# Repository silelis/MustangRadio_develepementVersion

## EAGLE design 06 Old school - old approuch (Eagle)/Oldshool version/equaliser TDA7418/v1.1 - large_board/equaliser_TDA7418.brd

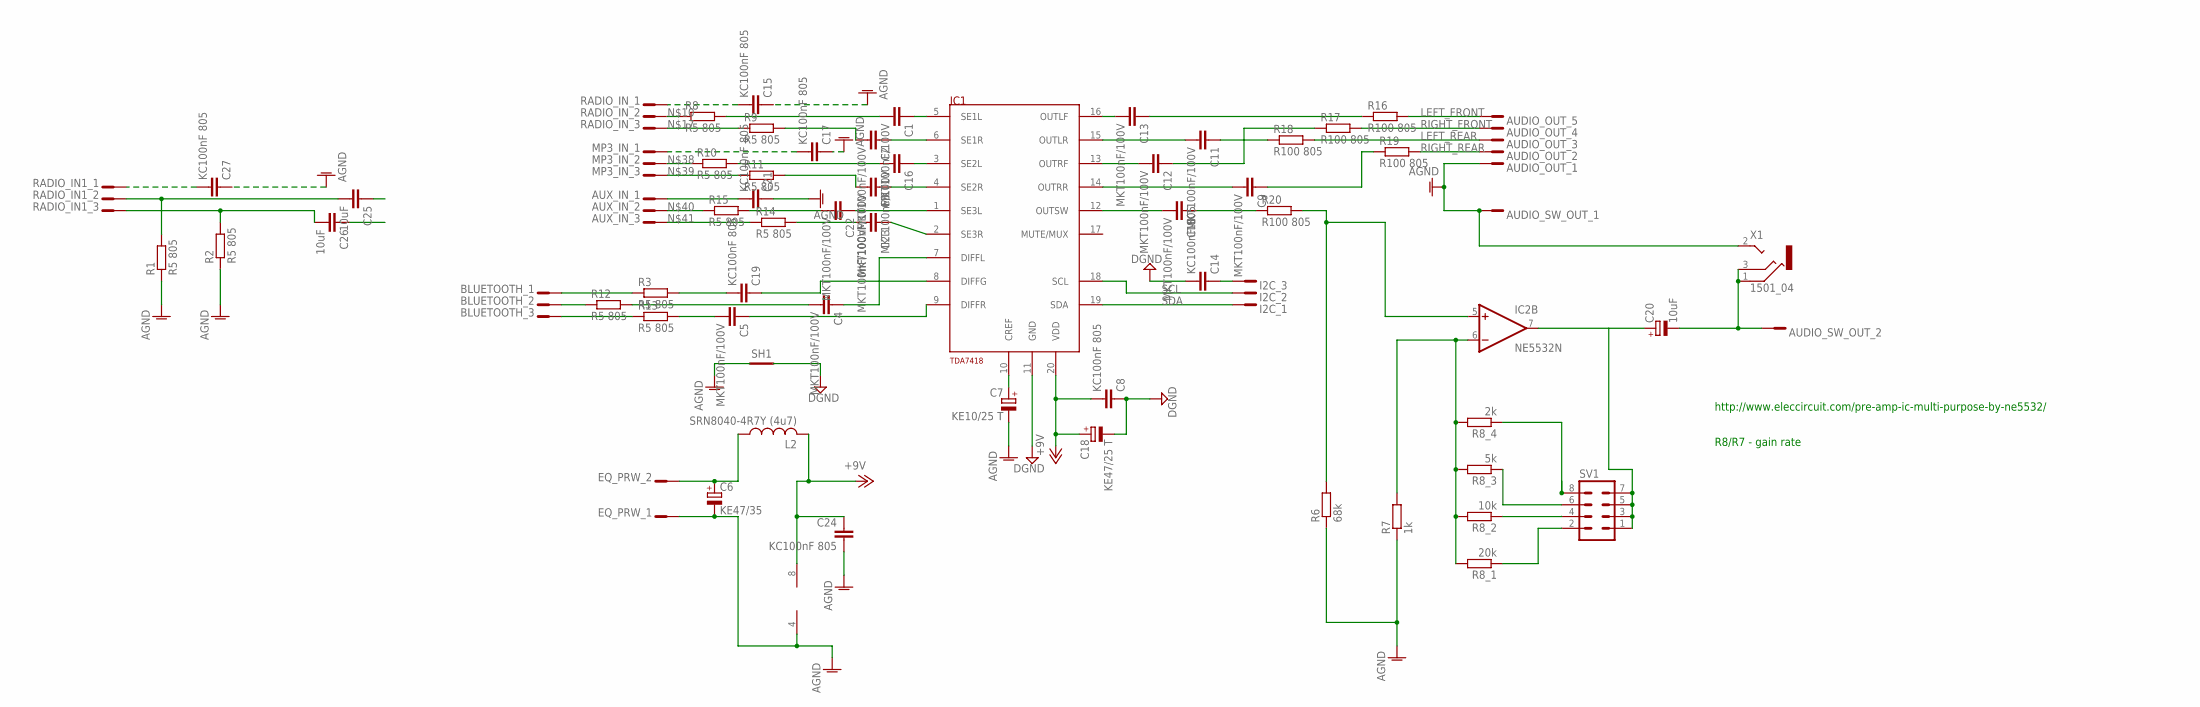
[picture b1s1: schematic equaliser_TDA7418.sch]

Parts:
AUDIO_OUT: JST_5_PIN_B5B-PH-KS; B5B-PH-KS
AUDIO_SW_OUT: JST_2_PIN_B2B-PH-KS; B2B-PH-KS
AUX_IN: JST_3_PIN_B3B-PH-KS; B3B-PH-KS
BLUETOOTH: JST_3_PIN_B3B-PH-KS; B3B-PH-KS
C1, C2, C3, C4, C5, C9, C10, C11, C12, C13, C16, C22, C23: MKT100nF/100V; C050-035X075
C6: KE47/35; TT2D6
C7: KE10/25 T; E1,8-4
C8, C14, C15, C17, C19, C21, C24, C27: KC100nF 805; C0805
C18: KE47/25 T; B45181B
C20: 10uF; TT2D6
C25, C26: 10uF; C050-035X075
EQ_PRW: JST_2_PIN_B2B-XH-A; B2B-XH-A
I2C: JST_3_PIN_B3B-PH-KS; B3B-PH-KS
IC1: TDA7418; SO20
IC2: NE5532N; DIL08
L2: SRN8040-4R7Y (4u7); 0204/5
MP3_IN: JST_3_PIN_B3B-PH-KS; B3B-PH-KS
R1, R2, R3, R8, R9, R10, R11, R12, R13, R14, R15: R5 805; R0805
R6: 68k; R0805
R7: 1k; R0805
R8_1: 20k; R0805
R8_2: 10k; R0805
R8_3: 5k; R0805
R8_4: 2k; R0805
R16, R17, R18, R19, R20: R100 805; R0805
RADIO_IN, RADIO_IN1: JST_3_PIN_B3B-PH-KS; B3B-PH-KS
SH1: SHORT-HT5; SHORT_TOP-50
SV1: MA04-2
X1: 1501_04; 1501_05

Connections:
+9V0: C8.2, C18.+, C24.1, IC1.20 (VDD), IC2.8 (V+), L2.2
AGND: AUDIO_OUT.P$1, AUDIO_SW_OUT.P$1, C6.-, C7.-, C15.1, C17.1, C21.1, C24.2, C27.1, EQ_PRW.P$1, IC2.4 (V-), R1.1, R2.1, R6.1, R7.1, SH1.1, X1.2
DGND: C8.1, C14.2, C18.-, IC1.11 (GND), SH1.2
L1: C1.2, R8.2
L2: C16.2, R10.2
L3: C4.2, R12.2
L4: C25.2, R1.2, RADIO_IN1.P$2
LEFT_FRONT: AUDIO_OUT.P$5, R16.2
LEFT_REAR: AUDIO_OUT.P$3, R18.2
unnamed: C6.+, EQ_PRW.P$2, L2.1
unnamed: R8_1.1, SV1.2
unnamed: C7.+, IC1.10 (CREF)
unnamed: C1.1, IC1.5 (SE1L)
unnamed: C2.1, IC1.6 (SE1R)
unnamed: C16.1, IC1.3 (SE2L)
unnamed: C3.1, IC1.4 (SE2R)
unnamed: C23.1, IC1.2 (SE3R)
unnamed: C22.1, IC1.1 (SE3L)
unnamed: R8.1, RADIO_IN.P$2
unnamed: AUDIO_SW_OUT.P$2, C20.-, X1.1, X1.3
unnamed: C13.2, IC1.16 (OUTLF)
unnamed: C11.2, IC1.15 (OUTLR)
unnamed: C11.1, R18.1
unnamed: C9.1, R19.1
unnamed: C12.2, IC1.13 (OUTRF)
unnamed: R9.1, RADIO_IN.P$3
unnamed: C9.2, IC1.14 (OUTRR)
unnamed: C10.2, IC1.12 (OUTSW)
unnamed: R8_2.1, SV1.4
unnamed: C20.+, IC2.7 (OUT), SV1.1, SV1.3, SV1.5, SV1.7
unnamed: R8_3.1, SV1.6
unnamed: C14.1, I2C.P$3
unnamed: C15.2, RADIO_IN.P$1
unnamed: C13.1, R16.1
unnamed: C17.2, MP3_IN.P$1
unnamed: BLUETOOTH.P$1, R3.1
unnamed: R8_4.1, SV1.8
unnamed: C4.1, IC1.7 (DIFFL)
unnamed: C5.1, IC1.9 (DIFFR)
unnamed: C22.2, R15.2
unnamed: AUX_IN.P$3, R14.1
unnamed: IC2.6 (-IN), R7.2, R8_1.2, R8_2.2, R8_3.2, R8_4.2
unnamed: IC2.5 (+IN), R6.2, R20.2
unnamed: C12.1, R17.1
unnamed: C10.1, R20.1
unnamed: MP3_IN.P$2, R10.1
unnamed: MP3_IN.P$3, R11.1
unnamed: BLUETOOTH.P$2, R12.1
unnamed: BLUETOOTH.P$3, R13.1
unnamed: AUX_IN.P$2, R15.1
unnamed: C23.2, R14.2
unnamed: C2.2, R9.2
unnamed: C3.2, R11.2
unnamed: C5.2, R13.2
unnamed: AUX_IN.P$1, C21.2
unnamed: C27.2, RADIO_IN1.P$1
unnamed: C19.1, IC1.8 (DIFFG)
unnamed: C26.2, R2.2, RADIO_IN1.P$3
unnamed: C19.2, R3.2
RIGHT_FRONT: AUDIO_OUT.P$4, R17.2
RIGHT_REAR: AUDIO_OUT.P$2, R19.2
SCL: I2C.P$2, IC1.18 (SCL)
SDA: I2C.P$1, IC1.19 (SDA)

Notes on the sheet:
http://www.eleccircuit.com/pre-amp-ic-multi-purpose-by-ne5532/
R8/R7 - gain rate

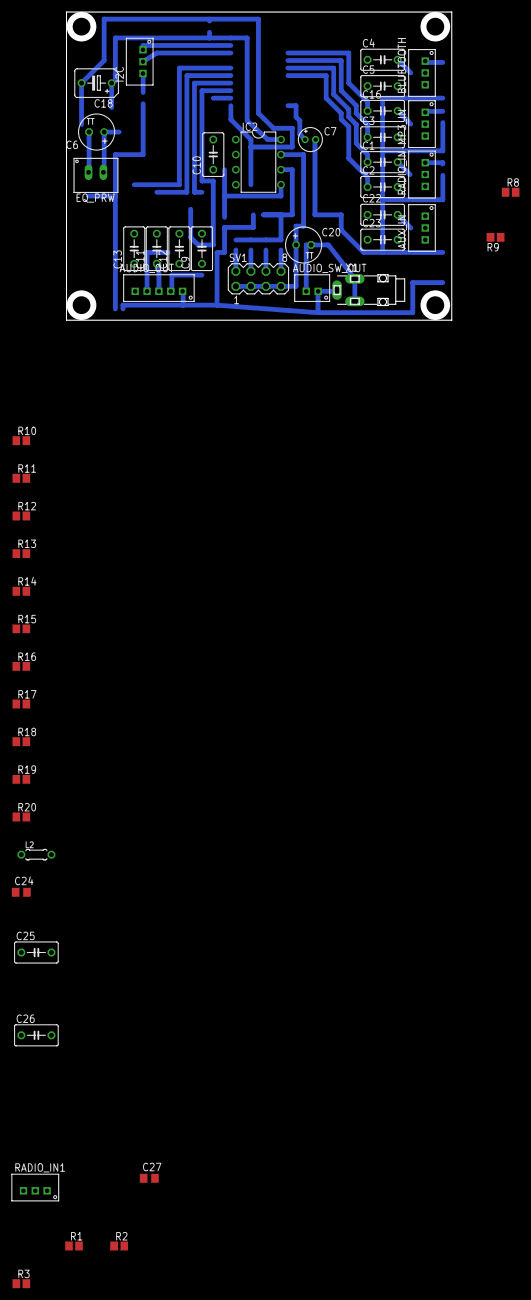
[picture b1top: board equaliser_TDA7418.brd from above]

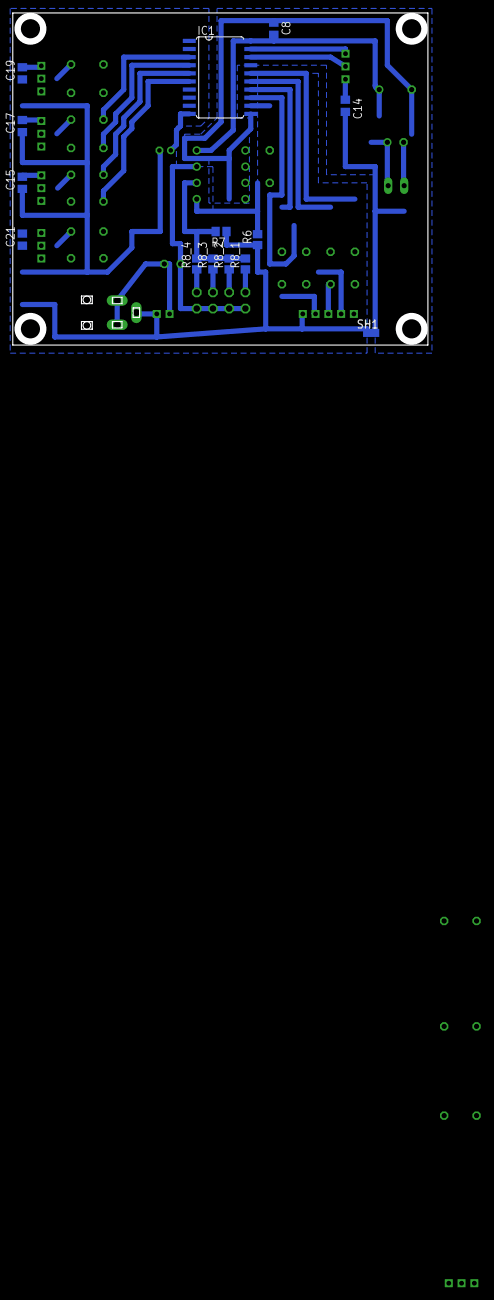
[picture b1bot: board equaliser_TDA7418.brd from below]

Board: 2 copper layers, 65.0 x 52.0 mm, 64 parts (14 on the bottom side), 63 nets.

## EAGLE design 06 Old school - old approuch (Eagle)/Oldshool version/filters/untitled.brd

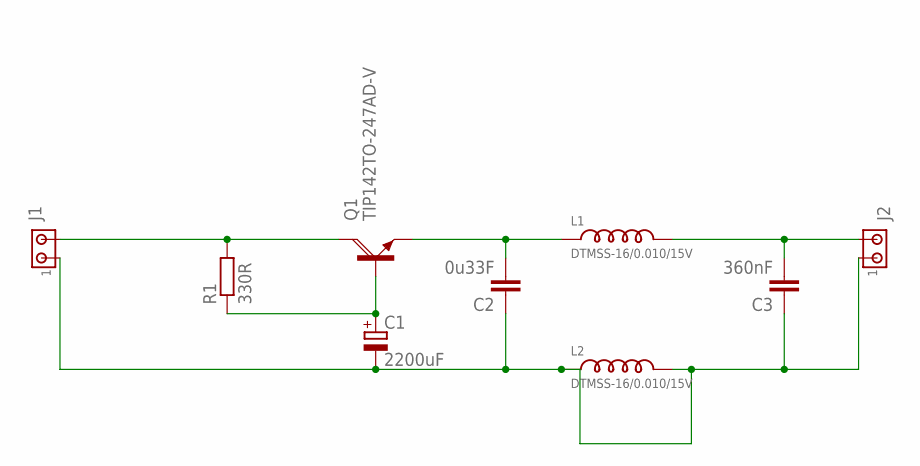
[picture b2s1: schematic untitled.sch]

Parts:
C1: 2200uF; E5-13
C2: 0u33F; C102-054X133
C3: 360nF; C102-054X133
J1, J2: MTA02-100; 10X02MTA
L1, L2: DTMSS-16/0.010/15V; DTMSS-16/0.010/15-V
Q1: TIP142TO-247AD-V; TO-247AD-V
R1: 330R; VTA52

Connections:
GND: C1.-, C2.1, C3.1, J1.1, J2.1, L2.P$1, L2.P$2
unnamed: J1.2, Q1.D (C), R1.2
unnamed: C1.+, Q1.G (B), R1.1
unnamed: C2.2, L1.P$1, Q1.S (E)
unnamed: C3.2, J2.2, L1.P$2

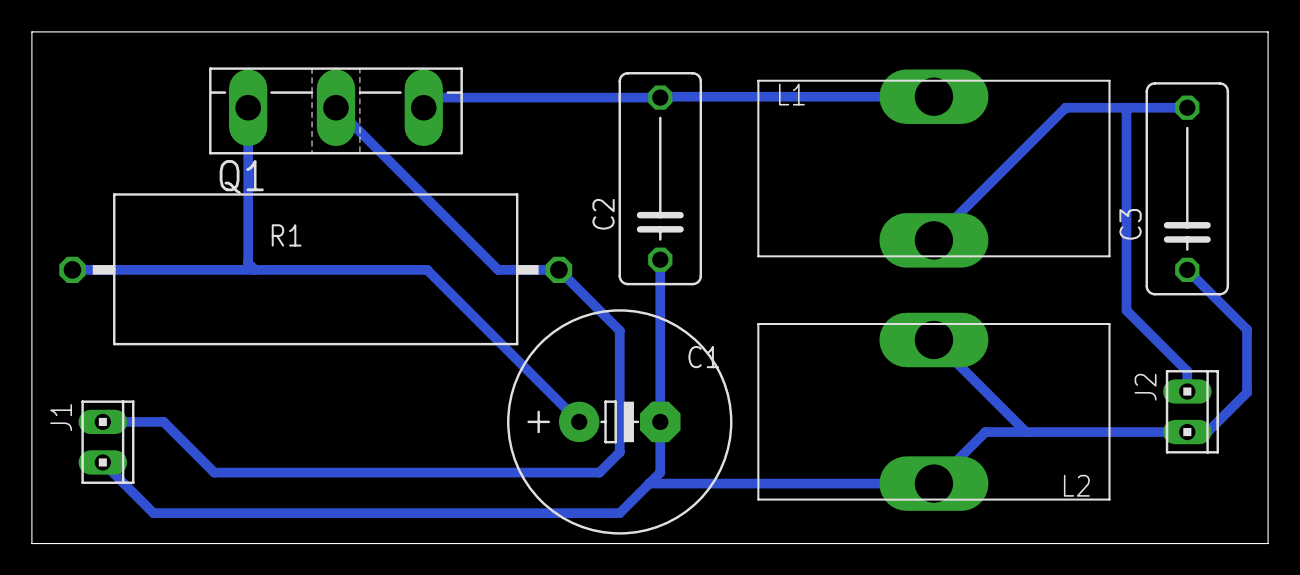
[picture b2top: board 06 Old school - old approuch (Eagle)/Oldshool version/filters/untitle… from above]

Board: 2 copper layers, 77.4 x 32.1 mm, 9 parts (0 on the bottom side), 5 nets.

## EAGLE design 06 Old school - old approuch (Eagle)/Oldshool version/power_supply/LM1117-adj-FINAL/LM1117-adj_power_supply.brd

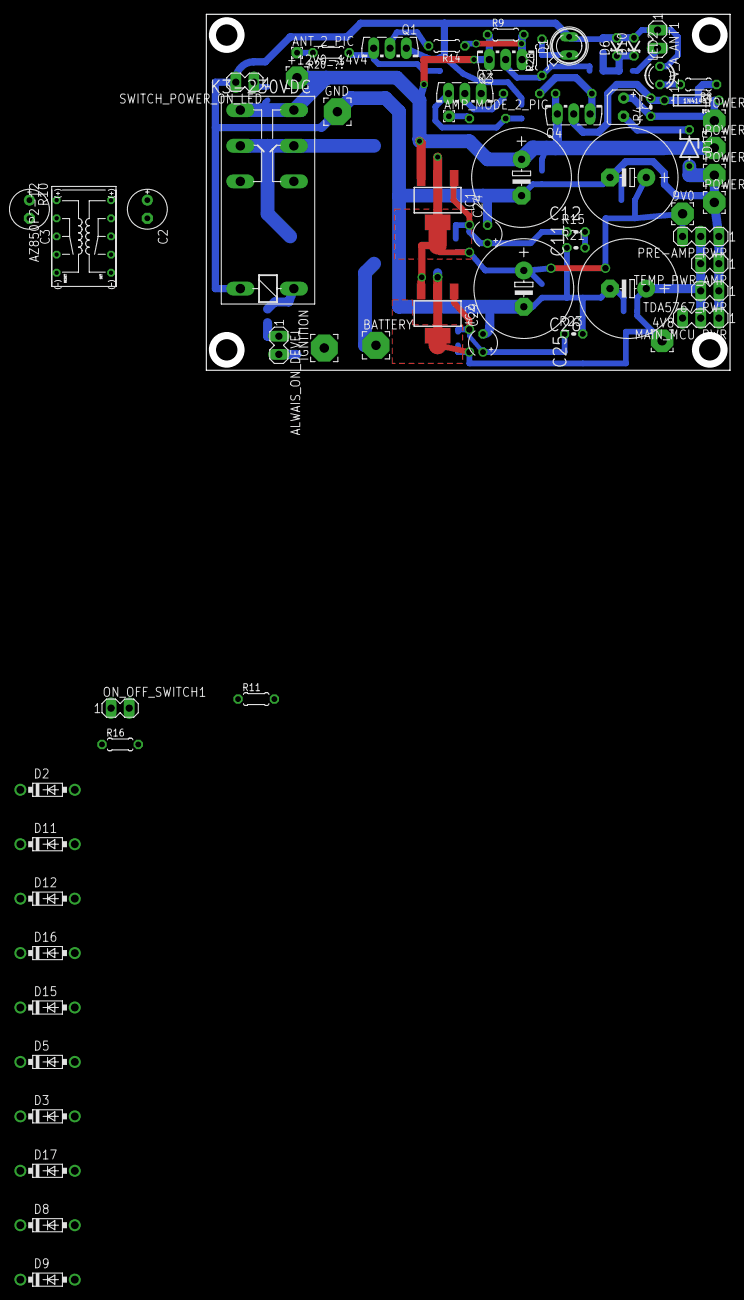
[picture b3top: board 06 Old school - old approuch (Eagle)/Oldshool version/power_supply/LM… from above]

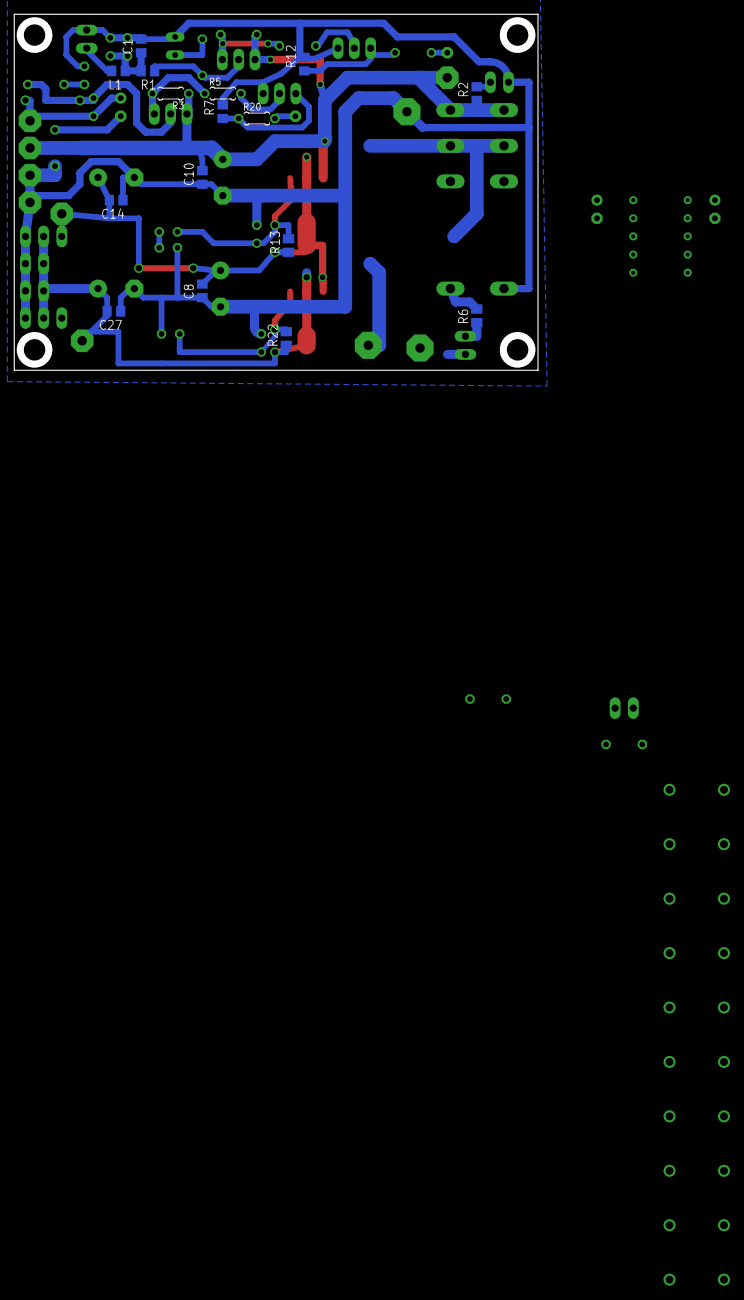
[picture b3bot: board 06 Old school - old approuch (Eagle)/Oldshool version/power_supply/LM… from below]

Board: 2 copper layers, 73.3 x 49.8 mm, 80 parts (16 on the bottom side), 36 nets.

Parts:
4V8, 9V0: 3,17/1,3
12V_A_ANT1: MA02-1
+12V0-14V4: 3,17/1,3
ALWAIS_ON_DEVEL: MA02-1
AMP_MODE_2_PIC: 1,6/0,8
ANT_2_PIC: 1,6/0,8
BATTERY: +14V4; 3,81/1,3
C1, C8, C10, C14, C27: KC100nF 805; C0805
C2, C3: 22-100uF/25V; E2,5-6E
C7: KE47/25 T; B45181A
C11, C12, C25, C26: KE2200/25; E5-13
C24, C29: KE10/50; TT2D4
D1: LED F2 G; SFH482
D2, D3, D5, D8, D9, D11, D12, D15, D16, D17: 1N4004; DO41-7.6
D6, D10: 1.3W12V; ZDIO-2.5
D13: 3.9V; ZDIO-5
D14: 1N4148; DO-1N4148
GND: GND; 3,81/1,3
IC1, IC2: LM1117MPX-ADJ; SOT223
IGNITION: +14V4; 3,81/1,3
K3-230VDC: AZ743-2CB-12DE; G2R2
L1: R600@100M; R0805
LED2: LED F3 B; LED3MM
MAIN_MCU_PWR: MA03-1
ON_OFF_SWITCH1: MA02-1
POWER_AMP_1, POWER_AMP_2, POWER_AMP_3: 3,17/1,3
POWER_AMP_MODE: 3,17/1,3
PRE-AMP_PWR: MA03-1
Q1, Q2: BD139; TO126AV
Q3, Q4: BD136; TO126AV
R1: R240 805; M0805
R2: R1K; R0805
R3, R9: R10K; 0204/5
R4: 10k; 0204V
R5: R4.7; 0204/5
R6: R??? 805 1; M0805
R7, R12: R10K 805; R0805
R8, R20, R20-??, R28: R1K; 0204/5
R10: AZ850P2-12; AZ850-2C
R11, R16: 2.2k-5k; 0204/5
R13, R22: R240 805 1; M0805
R14: R4.7K; 0204/5
R15, R21, R23: R680 1%; 0204V
SWITCH_POWER_ON_LED: MA02-1
TDA5767_PWR: MA02-1
TEMP_PWR_AMP: MA02-1

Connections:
+4V8: 4V8.1, C26.+, C27.2, D3.A, D17.C, IC2.2, IC2.TAB, MAIN_MCU_PWR.2, PRE-AMP_PWR.2, R22.1, TDA5767_PWR.2, TEMP_PWR_AMP.2
+9V0: 9V0.1, C8.2, C12.+, C14.2, C25.+, D3.C, D8.A, D9.C, IC1.2, IC1.TAB, IC2.3, PRE-AMP_PWR.3, R13.1
+14.4V: +12V0-14V4.1, C10.2, C11.+, D8.C, IC1.3, K3-230VDC.S1, K3-230VDC.S2, POWER_AMP_3.1, Q3.E, Q4.E, R2.1, R3.1, R9.1
AMP_MODE: AMP_MODE_2_PIC.1, R20.2
GND: 12V_A_ANT1.1, C1.2, C8.1, C10.1, C11.-, C12.-, C14.1, C24.-, C25.-, C26.-, C27.1, C29.-, D1.K, D5.A, D6.A, D10.A, D13.A, GND.1, K3-230VDC.2, LED2.K, MAIN_MCU_PWR.1, ON_OFF_SWITCH1.1, POWER_AMP_1.1, POWER_AMP_2.1, PRE-AMP_PWR.1, Q1.E, Q2.E, R7.2, R12.2, R21.1, R23.2, SWITCH_POWER_ON_LED.2, TDA5767_PWR.1, TEMP_PWR_AMP.1
MCLR_SUPPLY: ALWAIS_ON_DEVEL.1, R6.1, R10.P$7
MCLR_SUPPLY1: ALWAIS_ON_DEVEL.2, D15.C
unnamed: ANT_2_PIC.1, R20-??.2
unnamed: C24.+, D9.A, IC1.1, R13.2, R15.1
unnamed: R15.2, R21.2
unnamed: D2.A, D11.A, R10.P$5
unnamed: BATTERY.1, K3-230VDC.P1, K3-230VDC.P2, R10.P$3
unnamed: Q3.C, R1.1, R28.1
unnamed: D5.C, K3-230VDC.1, R6.2
unnamed: R2.2, SWITCH_POWER_ON_LED.1
unnamed: D14.C, Q4.C, R4.2, R8.1
unnamed: D15.A, IGNITION.1
unnamed: C2.+, D2.C, R10.P$1, R11.1
unnamed: C3.+, D16.C, R10.P$10, R16.1
unnamed: Q1.B, R12.1, R20-??.1
unnamed: Q1.C, R14.2
unnamed: C2.-, C3.-, D11.C, D12.C, ON_OFF_SWITCH1.2
unnamed: C7.-, D13.C
unnamed: C7.+, D14.A, POWER_AMP_MODE.1, R4.1
unnamed: D12.A, D16.A, R10.P$6
unnamed: Q3.B, R9.2, R14.1
unnamed: C1.1, D6.C, D10.C, L1.1, R1.2
unnamed: C29.+, D17.A, IC2.1, R22.2, R23.1
unnamed: R10.P$4, R11.2
unnamed: R10.P$2, R16.2
unnamed: 12V_A_ANT1.2, L1.2
unnamed: D1.A, R28.2
unnamed: Q2.B, R7.1, R20.1
unnamed: Q2.C, R5.2
unnamed: Q4.B, R3.2, R5.1
unnamed: LED2.A, R8.2

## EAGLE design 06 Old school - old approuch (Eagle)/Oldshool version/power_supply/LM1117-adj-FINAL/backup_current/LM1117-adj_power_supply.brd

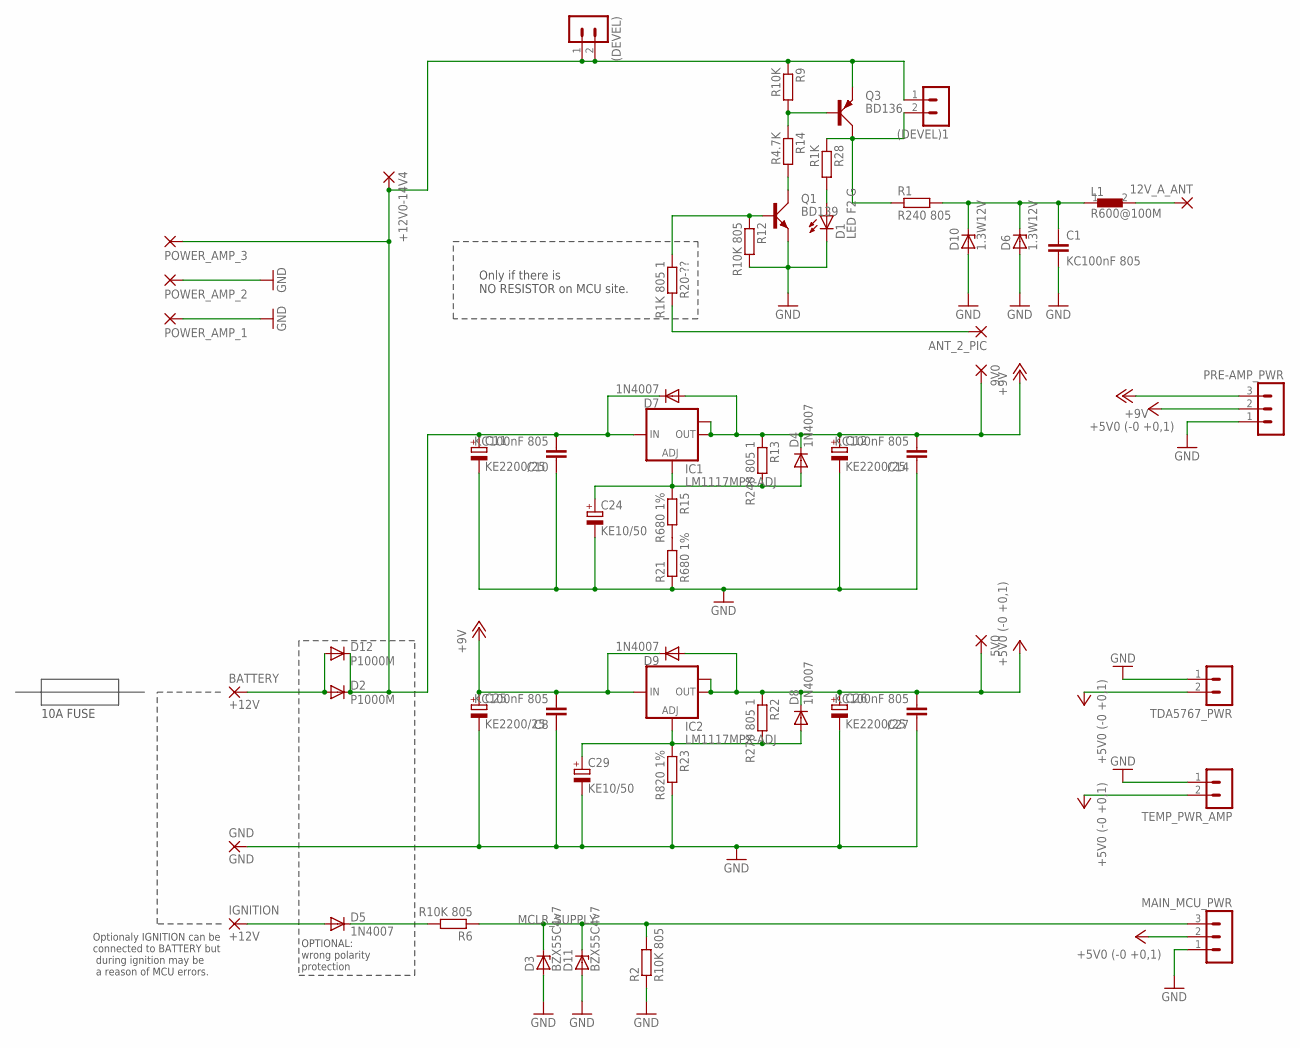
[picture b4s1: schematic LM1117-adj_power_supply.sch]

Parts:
5V0, 9V0, 12V_A_ANT: 3,17/1,3
(DEVEL), (DEVEL)1: MA02-1
+12V0-14V4: 3,17/1,3
ANT_2_PIC: 1,6/0,8
BATTERY: +12V; 3,81/1,3
C1, C8, C10, C14, C27: KC100nF 805; C0805
C11, C12, C25, C26: KE2200/25; E5-13
C24, C29: KE10/50; TT2D4
D1: LED F2 G; SFH482
D2, D12: P1000M; P6-15
D3, D11: BZX55C4v7; ZDIO-2.5
D4, D8: 1N4007; D-2.5
D5, D7, D9: 1N4007; D-5
D6, D10: 1.3W12V; ZDIO-2.5
GND: GND; 3,81/1,3
IC1, IC2: LM1117MPX-ADJ; SOT223
IGNITION: +12V; 3,81/1,3
L1: R600@100M; R0805
MAIN_MCU_PWR: MA03-1
POWER_AMP_1, POWER_AMP_2, POWER_AMP_3: 3,17/1,3
PRE-AMP_PWR: MA03-1
Q1: BD139; TO126AV
Q3: BD136; TO126AV
R1: R240 805; M0805
R2, R6, R12: R10K 805; R0805
R9: R10K; 0204/5
R13: R240 805 1; M0805
R14: R4.7K; 0204/5
R15, R21: R680 1%; 0204V
R20-??: R1K 805 1; 0204V
R22: R270 805 1; M0805
R23: R820 1%; 0204V
R28: R1K; 0204/5
TDA5767_PWR: MA02-1
TEMP_PWR_AMP: MA02-1

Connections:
+5V: 5V0.1, C26.+, C27.2, D8.C, D9.A, IC2.2 (OUT), IC2.TAB (OUT1), MAIN_MCU_PWR.2, PRE-AMP_PWR.2, R22.1, TDA5767_PWR.2, TEMP_PWR_AMP.2
+12V: 9V0.1, C8.2, C12.+, C14.2, C25.+, D4.C, D7.A, D9.C, IC1.2 (OUT), IC1.TAB (OUT1), IC2.3 (IN), PRE-AMP_PWR.3, R13.1
+14.4V: (DEVEL).1, (DEVEL).2, (DEVEL)1.1, +12V0-14V4.1, C10.2, C11.+, D2.C, D7.C, D12.C, IC1.3 (IN), POWER_AMP_3.1, Q3.E, R9.1
GND: C1.2, C8.1, C10.1, C11.-, C12.-, C14.1, C24.-, C25.-, C26.-, C27.1, C29.-, D1.K (C), D3.A, D6.A, D10.A, D11.A, GND.1, MAIN_MCU_PWR.1, POWER_AMP_1.1, POWER_AMP_2.1, PRE-AMP_PWR.1, Q1.E, R2.1, R12.2, R21.1, R23.2, TDA5767_PWR.1, TEMP_PWR_AMP.1
MCLR_SUPPLY: D3.C, D11.C, MAIN_MCU_PWR.3, R2.2, R6.1
unnamed: ANT_2_PIC.1, R20-??.2
unnamed: C24.+, D4.A, IC1.1 (ADJ), R13.2, R15.1
unnamed: R15.2, R21.2
unnamed: BATTERY.1, D2.A, D12.A
unnamed: (DEVEL)1.2, Q3.C, R1.1, R28.1
unnamed: D5.A, IGNITION.1
unnamed: D5.C, R6.2
unnamed: Q1.B, R12.1, R20-??.1
unnamed: Q1.C, R14.2
unnamed: Q3.B, R9.2, R14.1
unnamed: C1.1, D6.C, D10.C, L1.1, R1.2
unnamed: C29.+, D8.A, IC2.1 (ADJ), R22.2, R23.1
unnamed: 12V_A_ANT.1, L1.2
unnamed: D1.A, R28.2

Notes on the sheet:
10A FUSE
Optionaly IGNITION can be connected to BATTERY but during ignition may be a reason of MCU errors.
OPTIONAL: wrong polarity protection
Only if there is NO RESISTOR on MCU site.

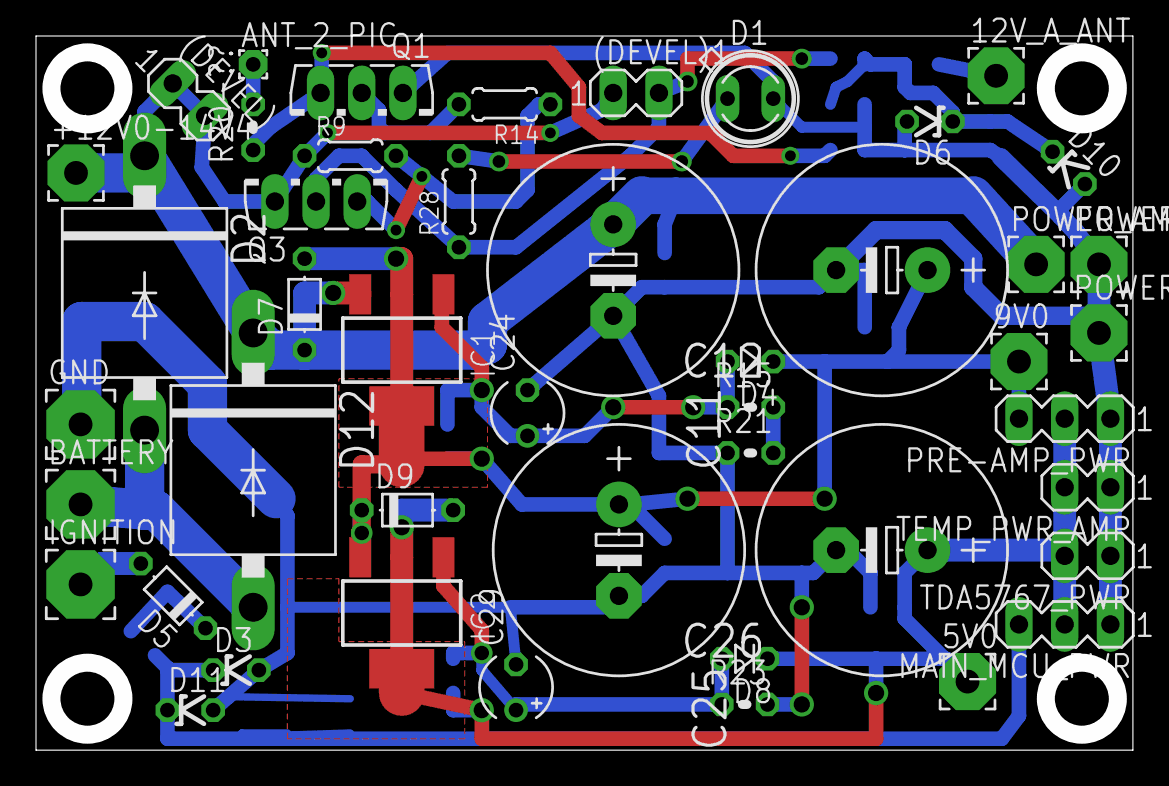
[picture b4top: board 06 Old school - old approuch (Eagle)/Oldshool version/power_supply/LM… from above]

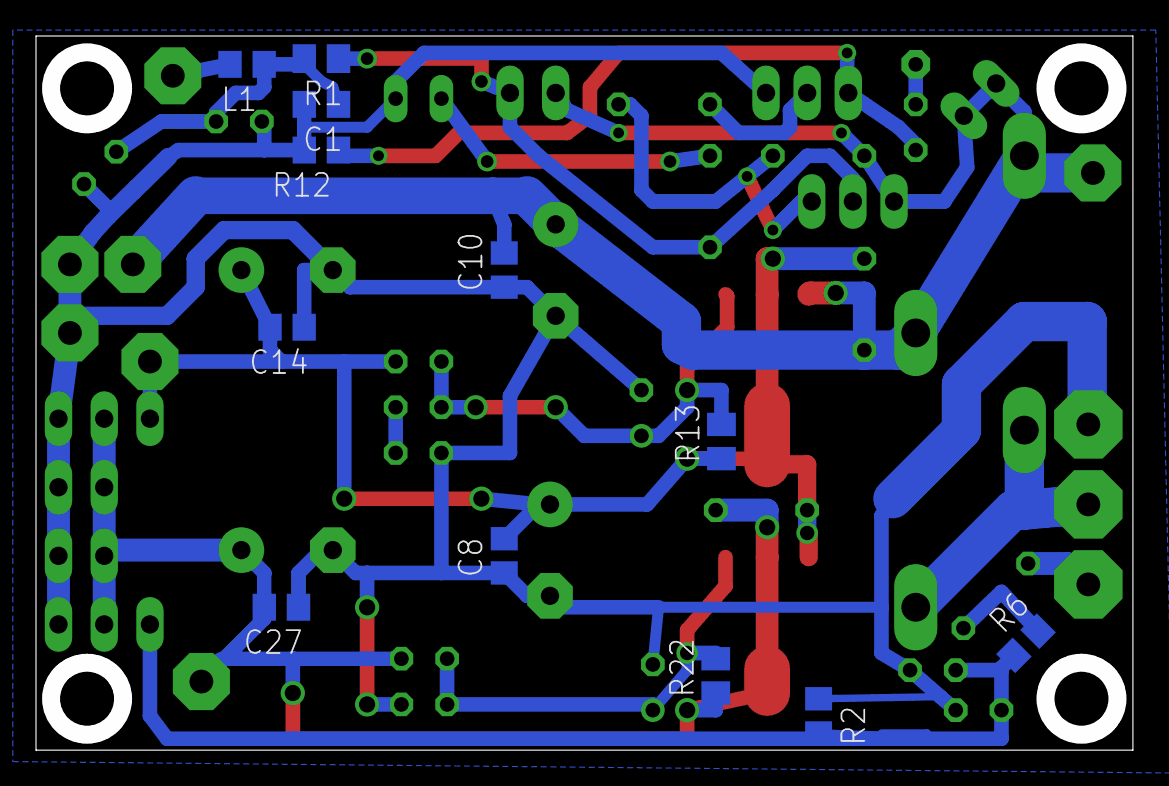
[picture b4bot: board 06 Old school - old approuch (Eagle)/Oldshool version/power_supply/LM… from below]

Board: 2 copper layers, 60.9 x 39.7 mm, 58 parts (12 on the bottom side), 19 nets.

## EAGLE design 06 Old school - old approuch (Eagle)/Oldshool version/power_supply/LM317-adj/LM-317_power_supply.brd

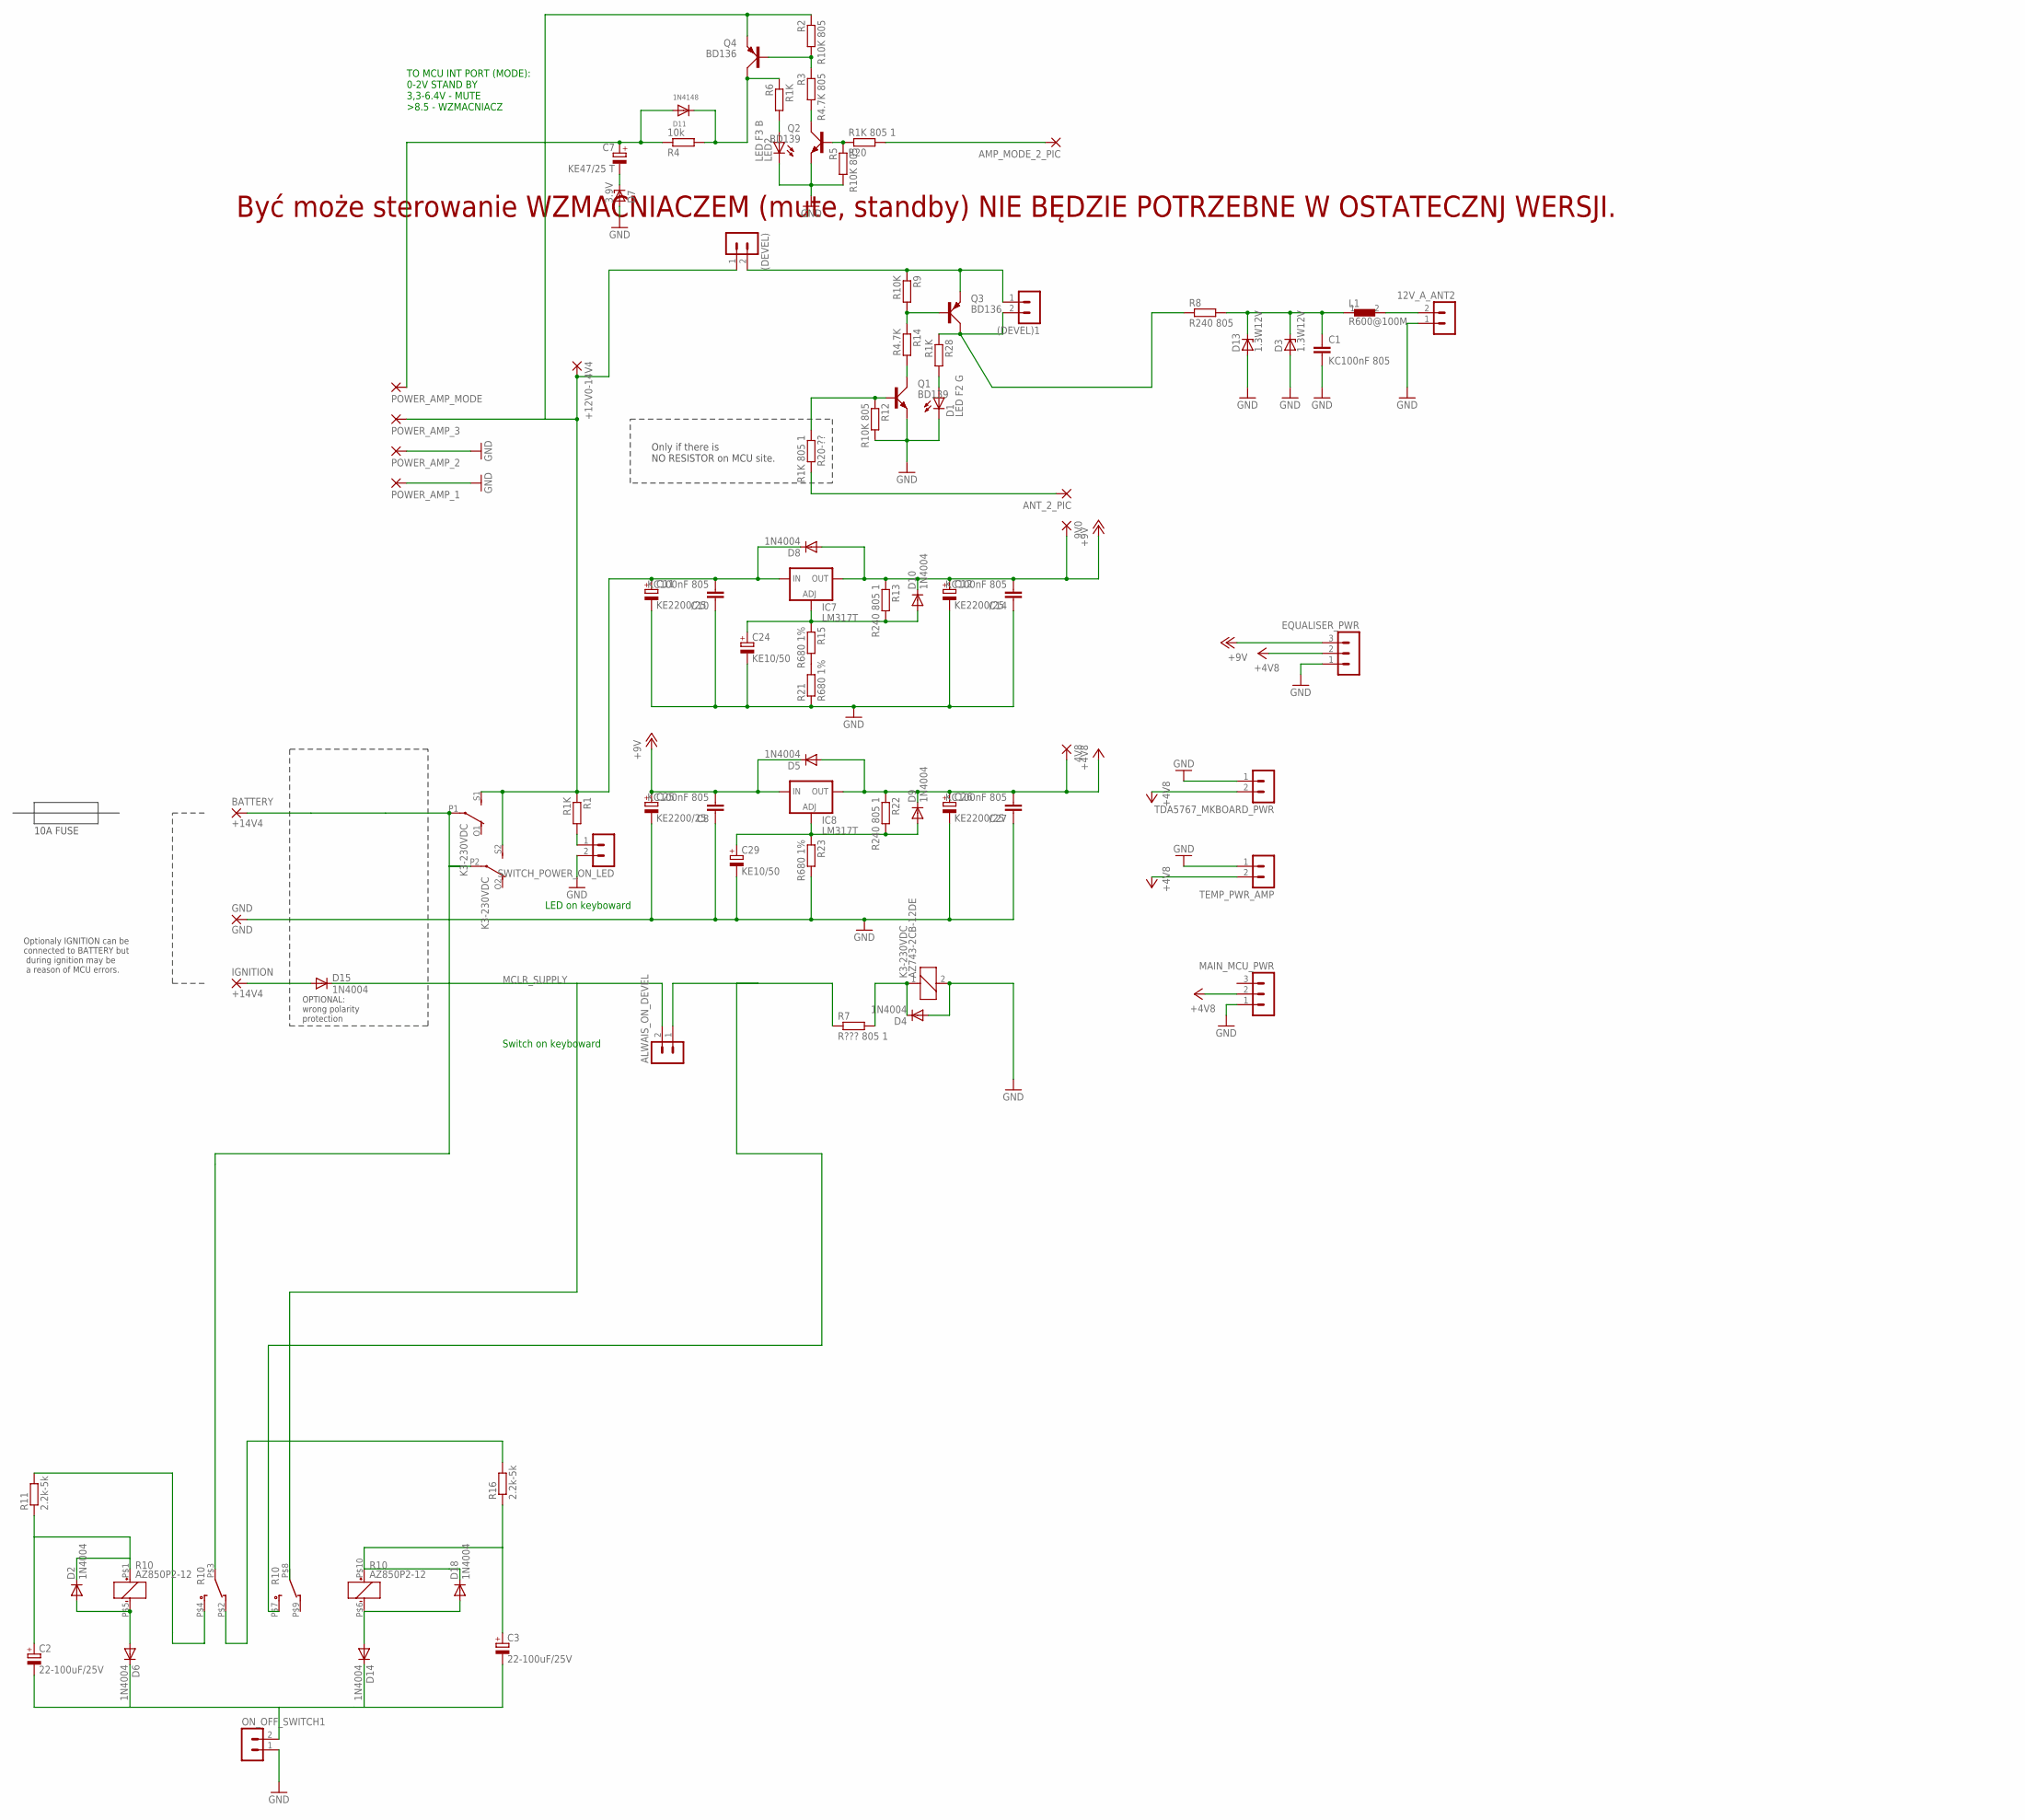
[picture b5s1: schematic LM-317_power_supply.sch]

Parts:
4V8, 9V0: 3,17/1,3
12V_A_ANT2: MA02-1
(DEVEL), (DEVEL)1: MA02-1
+12V0-14V4: 3,17/1,3
ALWAIS_ON_DEVEL: MA02-1
AMP_MODE_2_PIC: 1,6/0,8
ANT_2_PIC: 1,6/0,8
BATTERY: +14V4; 3,81/1,3
C1, C8, C10, C14, C27: KC100nF 805; C0805
C2, C3: 22-100uF/25V; E2,5-6E
C7: KE47/25 T; B45181A
C11, C12, C25, C26: KE2200/25; E3,5-8
C24, C29: KE10/50; TT2D4
D1: LED F2 G; SFH482
D2, D4, D5, D6, D8, D9, D10, D14, D15, D18: 1N4004; DO41-7.6
D3, D13: 1.3W12V; ZDIO-2.5
D7: 3.9V; ZDIO-5
D11: 1N4148; DO-1N4148
EQUALISER_PWR: MA03-1
GND: GND; 3,81/1,3
IC7, IC8: LM317T; 317TS
IGNITION: +14V4; 3,81/1,3
K3-230VDC: AZ743-2CB-12DE; G2R2
L1: R600@100M; R0805
LED2: LED F3 B; LED3MM
MAIN_MCU_PWR: MA03-1
ON_OFF_SWITCH1: MA02-1
POWER_AMP_1, POWER_AMP_2, POWER_AMP_3: 3,17/1,3
POWER_AMP_MODE: 3,17/1,3
Q1, Q2: BD139; TO126AV
Q3, Q4: BD136; TO126AV
R1, R28: R1K; 0204/7
R2, R5, R12: R10K 805; R0805
R3: R4.7K 805; R0805
R4: 10k; 0204/5
R6: R1K; 0204V
R7: R??? 805 1; M0805
R8: R240 805; M0805
R9: R10K; 0204/5
R10: AZ850P2-12; AZ850-2C
R11, R16: 2.2k-5k; 0204/5
R13, R22: R240 805 1; M0805
R14: R4.7K; 0204/5
R15, R21, R23: R680 1%; 0204/5
R20: R1K 805 1; R0805
R20-??: R1K 805 1; 0204V
SWITCH_POWER_ON_LED: MA02-1
TDA5767_MKBOARD_PWR: MA02-1
TEMP_PWR_AMP: MA02-1

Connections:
+4V8: 4V8.1, C26.+, C27.2, D5.A, D9.C, EQUALISER_PWR.2, IC8.2 (OUT), MAIN_MCU_PWR.2, R22.1, TDA5767_MKBOARD_PWR.2, TEMP_PWR_AMP.2
+9V: 9V0.1, C8.2, C12.+, C14.2, C25.+, D5.C, D8.A, D10.C, EQUALISER_PWR.3, IC7.2 (OUT), IC8.3 (IN), R13.1
+14.4V: (DEVEL).1, +12V0-14V4.1, C10.2, C11.+, D8.C, IC7.3 (IN), K3-230VDC.S1 (S), K3-230VDC.S2 (S), POWER_AMP_3.1, Q4.E, R1.1, R2.1
AMP_MODE: AMP_MODE_2_PIC.1, R20.2
GND: 12V_A_ANT2.1, C1.2, C8.1, C10.1, C11.-, C12.-, C14.1, C24.-, C25.-, C26.-, C27.1, C29.-, D1.K (C), D3.A, D4.A, D7.A, D13.A, EQUALISER_PWR.1, GND.1, K3-230VDC.2, LED2.K (C), MAIN_MCU_PWR.1, ON_OFF_SWITCH1.1, POWER_AMP_1.1, POWER_AMP_2.1, Q1.E, Q2.E, R5.2, R12.2, R21.1, R23.2, SWITCH_POWER_ON_LED.2, TDA5767_MKBOARD_PWR.1, TEMP_PWR_AMP.1
MCLR_SUPPLY: ALWAIS_ON_DEVEL.2, D15.C
unnamed: ANT_2_PIC.1, R20-??.2
unnamed: C24.+, D10.A, IC7.1 (ADJ), R13.2, R15.1
unnamed: R15.2, R21.2
unnamed: (DEVEL).2, (DEVEL)1.1, Q3.E, R9.1
unnamed: BATTERY.1, K3-230VDC.P1, K3-230VDC.P2, R10.P$3 (5)
unnamed: D4.C, K3-230VDC.1, R7.2
unnamed: ALWAIS_ON_DEVEL.1, R7.1, R10.P$7 (6)
unnamed: R1.2, SWITCH_POWER_ON_LED.1
unnamed: D11.C, Q4.C, R4.2, R6.1
unnamed: C1.1, D3.C, D13.C, L1.1, R8.2
unnamed: 12V_A_ANT2.2, L1.2
unnamed: D15.A, IGNITION.1
unnamed: C2.+, D2.C, R10.P$1 (+), R11.1
unnamed: D2.A, D6.A, R10.P$5 (-)
unnamed: C3.+, D18.C, R10.P$10 (+), R16.1
unnamed: Q1.B, R12.1, R20-??.1
unnamed: Q1.C, R14.2
unnamed: C2.-, C3.-, D6.C, D14.C, ON_OFF_SWITCH1.2
unnamed: C7.-, D7.C
unnamed: C7.+, D11.A, POWER_AMP_MODE.1, R4.1
unnamed: D14.A, D18.A, R10.P$6 (-)
unnamed: Q3.B, R9.2, R14.1
unnamed: (DEVEL)1.2, Q3.C, R8.1, R28.1
unnamed: C29.+, D9.A, IC8.1 (ADJ), R22.2, R23.1
unnamed: R10.P$4 (6), R11.2
unnamed: R10.P$2 (4), R16.2
unnamed: D1.A, R28.2
unnamed: Q2.B, R5.1, R20.1
unnamed: Q2.C, R3.2
unnamed: Q4.B, R2.2, R3.1
unnamed: LED2.A, R6.2

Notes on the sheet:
10A FUSE
Optionaly IGNITION can be connected to BATTERY but during ignition may be a reason of MCU errors.
OPTIONAL: wrong polarity protection
Only if there is NO RESISTOR on MCU site.
Switch on keyboward
LED on keyboward
TO MCU INT PORT (MODE): 0-2V STAND BY 3,3-6.4V - MUTE >8.5 - WZMACNIACZ
Być może sterowanie WZMACNIACZEM (mute, standby) NIE BĘDZIE POTRZEBNE W OSTATECZNJ WERSJI.

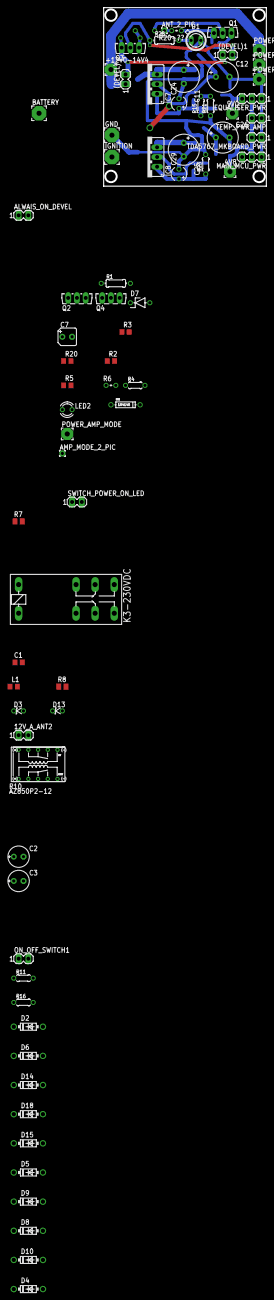
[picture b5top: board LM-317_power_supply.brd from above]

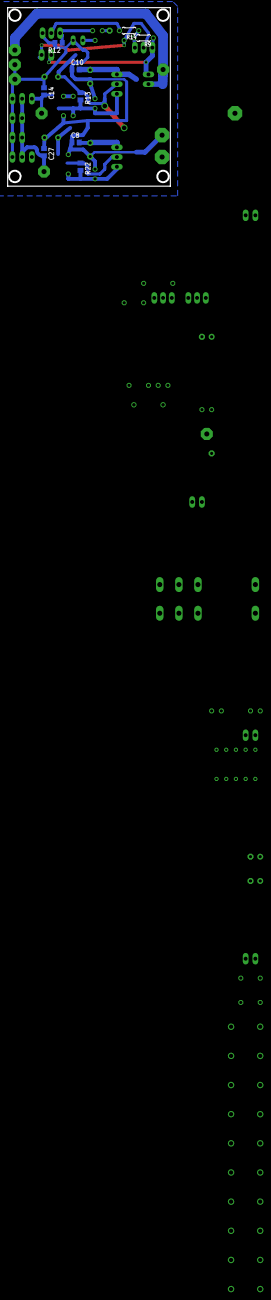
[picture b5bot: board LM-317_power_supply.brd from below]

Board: 2 copper layers, 42.5 x 46.7 mm, 82 parts (9 on the bottom side), 37 nets.

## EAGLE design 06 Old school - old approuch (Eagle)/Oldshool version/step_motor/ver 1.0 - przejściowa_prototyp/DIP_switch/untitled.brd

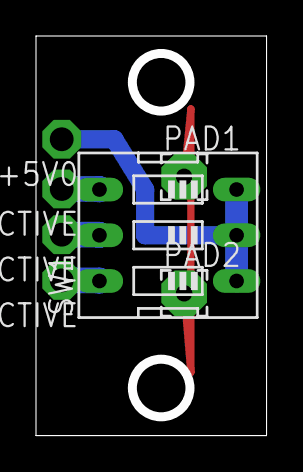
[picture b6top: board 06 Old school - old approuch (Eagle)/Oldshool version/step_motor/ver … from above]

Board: 2 copper layers, 12.8 x 22.2 mm, 7 parts (0 on the bottom side), 5 nets.

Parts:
+5V0: TPPAD1-13; P1-13
IS_DAB_ANT_ACTIVE: TPPAD1-13; P1-13
IS_FM_ANT_ACTIVE: TPPAD1-13; P1-13
IS_FM_DAB_CONVERTER_ACTIVE: TPPAD1-13; P1-13
PAD1, PAD2: WIREPAD2,54/0,9; 2,54/0,9
SW1: EDG-03

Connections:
unnamed: +5V0.TP, SW1.1, SW1.2, SW1.3
unnamed: IS_FM_ANT_ACTIVE.TP, SW1.6
unnamed: IS_DAB_ANT_ACTIVE.TP, SW1.5
unnamed: IS_FM_DAB_CONVERTER_ACTIVE.TP, SW1.4
STRUCTURAL_REINFORCEMENT: PAD1.1, PAD2.1
